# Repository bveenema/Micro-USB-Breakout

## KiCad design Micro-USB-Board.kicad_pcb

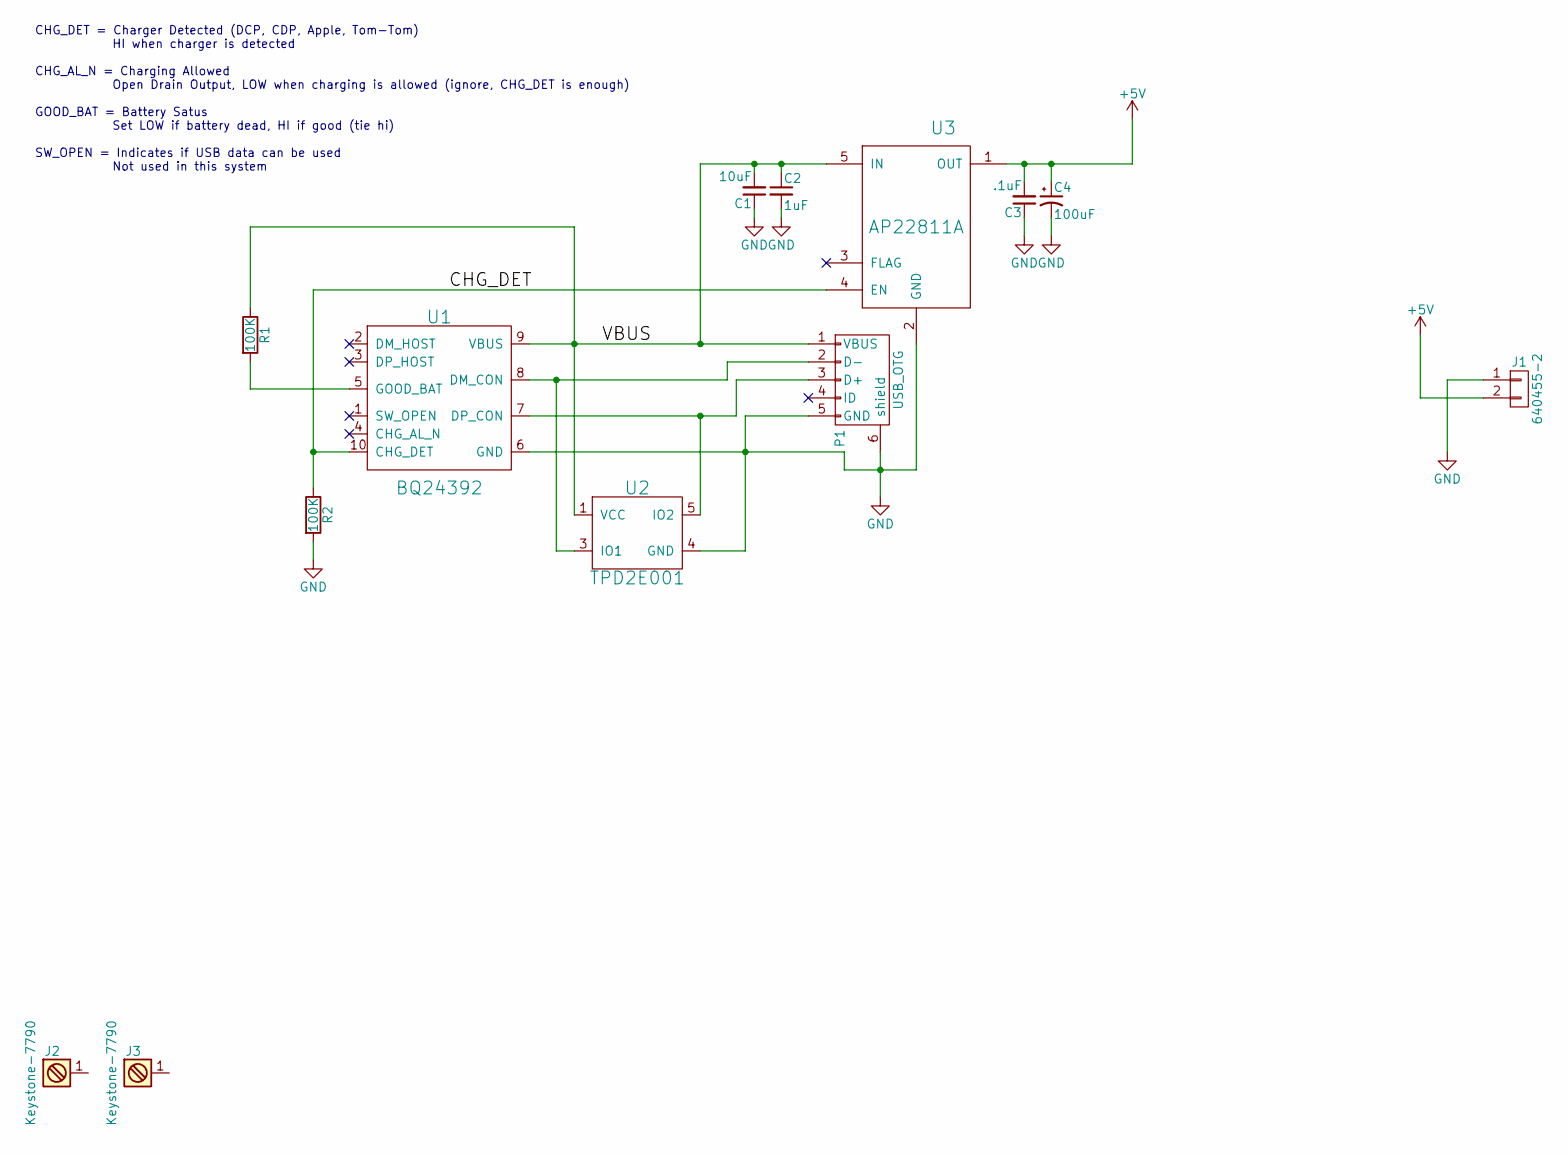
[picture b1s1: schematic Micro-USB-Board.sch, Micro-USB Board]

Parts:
C1: 10uF; C_0805; MPN CL21A106KPFNNNG
C2: 1uF; C_0805; MPN CL21B105KOFNNNG
C3: .1uF; C_0603; MPN CL10B104KO8NNNC
C4: 100uF; CP_Tantalum_Case-A_EIA-3216-18_Reflow; MPN F930J107KAA
J1: 640455-2
J2, J3: Keystone-7790; 7790-ScrewTerm-M3
P1: USB_OTG; USB_Micro-B_10103594-0001LF; MPN 10103594-0001LF
R1, R2: 100K; R_0805; MPN RMCF0805JT100K
U1: BQ24392; Texas_R_PUQFN-N10; MPN BQ24392RSER
U2: TPD2E001; SOT-23-5; MPN TPD2E001DRSR
U3: AP22811A; SOT-23-5

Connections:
+5V: C3.2, C4.1, J1.2, U3.1 (OUT)
/CHG_DET: R2.1, U1.10 (CHG_DET), U3.4 (EN)
/VBUS: C1.2, C2.1, P1.1 (VBUS), R1.1, U1.9 (VBUS), U2.1 (VCC), U3.5 (IN)
GND: C1.1, C2.2, C3.1, C4.2, J1.1, P1.5 (GND), P1.6 (shield), R2.2, U1.6 (GND), U2.4 (GND), U3.2 (GND)
unnamed: P1.2 (D-), U1.8 (DM_CON), U2.3 (IO1)
unnamed: P1.3 (D+), U1.7 (DP_CON), U2.5 (IO2)
unnamed: R1.2, U1.5 (GOOD_BAT)

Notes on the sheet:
CHG_DET = Charger Detected (DCP, CDP, Apple, Tom-Tom) HI when charger is detected CHG_AL_N = Charging Allowed Open Drain Output, LOW when charging is allowed (ignore, CHG_DET is enough) GOOD_BAT = Battery Satus Set LOW if battery dead, HI if good (tie hi) SW_OPEN = Indicates if USB data can be used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

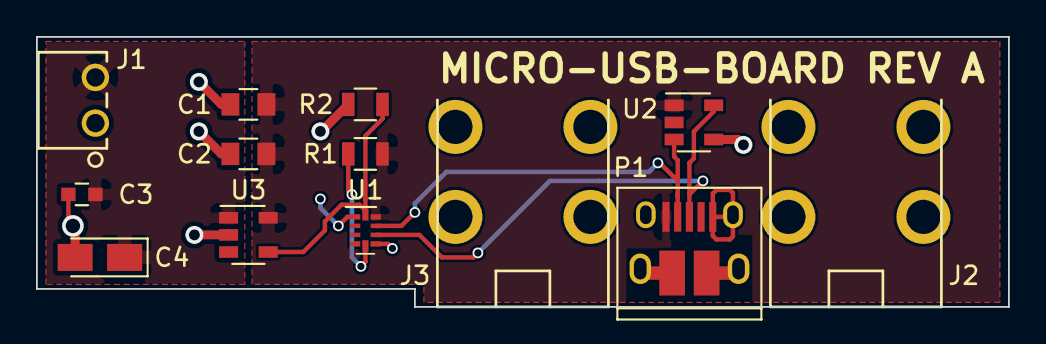
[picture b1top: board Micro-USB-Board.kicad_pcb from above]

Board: 2 copper layers, 54.0 x 15.0 mm, 13 parts (0 on the bottom side), 7 nets.

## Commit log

2018-04-12 Initial Commit - Rev A
2018-04-12 Created 3D
2018-04-13 Swapped Pos and Neg pins on J1 - Rev B
2018-04-13 update PRO file
2018-04-13 Added alternate components for passives to BOM

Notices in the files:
parts and their libraries:
Copyright 2016 Accelerated Designs. All rights reserved.
